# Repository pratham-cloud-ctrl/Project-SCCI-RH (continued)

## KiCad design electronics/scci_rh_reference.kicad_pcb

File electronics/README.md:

# SCCI_RH analog reference

An editable, routed **5 V artificial-signal / electrical-test-load circuit**.
It is one recording channel and one fixed-current biphasic load channel. It is
not implant electronics and contains no populated ADC, processor or biological
interface.

Open **`scci_rh_reference.kicad_pro`** in KiCad 10.0.6 or later. Local symbols,
footprints and component STEP models accompany the project. The 80 x 50 x
1.6 mm board has four 3.2 mm mounting holes at (10,10), (70,10), (10,40), (70,40).

- [Circuit explanation and boundaries](../docs/electronics.md)
- [Schematic PDF](exports/scci_rh_reference_schematic.pdf)
- [BOM](bom.csv)
- [Native board](scci_rh_reference.kicad_pcb)
- [Board STEP](exports/scci_rh_reference.step)
- [Gerber and drill reference exports](exports/gerbers/)
- [ERC report](reports/erc.json) and [DRC/parity report](reports/drc.json)
- [Model parameters](simulation/parameters.json) and [results](simulation/metrics.json)
- [Generic-device SPICE circuit](simulation/current_sink_generic.cir)
- [Third-party library licenses](THIRD_PARTY_LICENSES.md)

The retained reports have zero ERC violations, zero PCB DRC violations, zero
unconnected items and zero schematic parity issues, with no excluded violations.
Those checks establish connectivity/layout consistency, not analog stability.
The generic-device SPICE study exposed an unprotected switching transient;
revision B adds two 12 kΩ output resistors and reduces the nominal modeled peak
from 1361.36 to 102.58 μA. The before/after evidence is retained. The load and
parasitic assumptions remain conditional; no universal current cap is claimed.
Do not infer fabrication readiness or biological safety from a clean rule report.

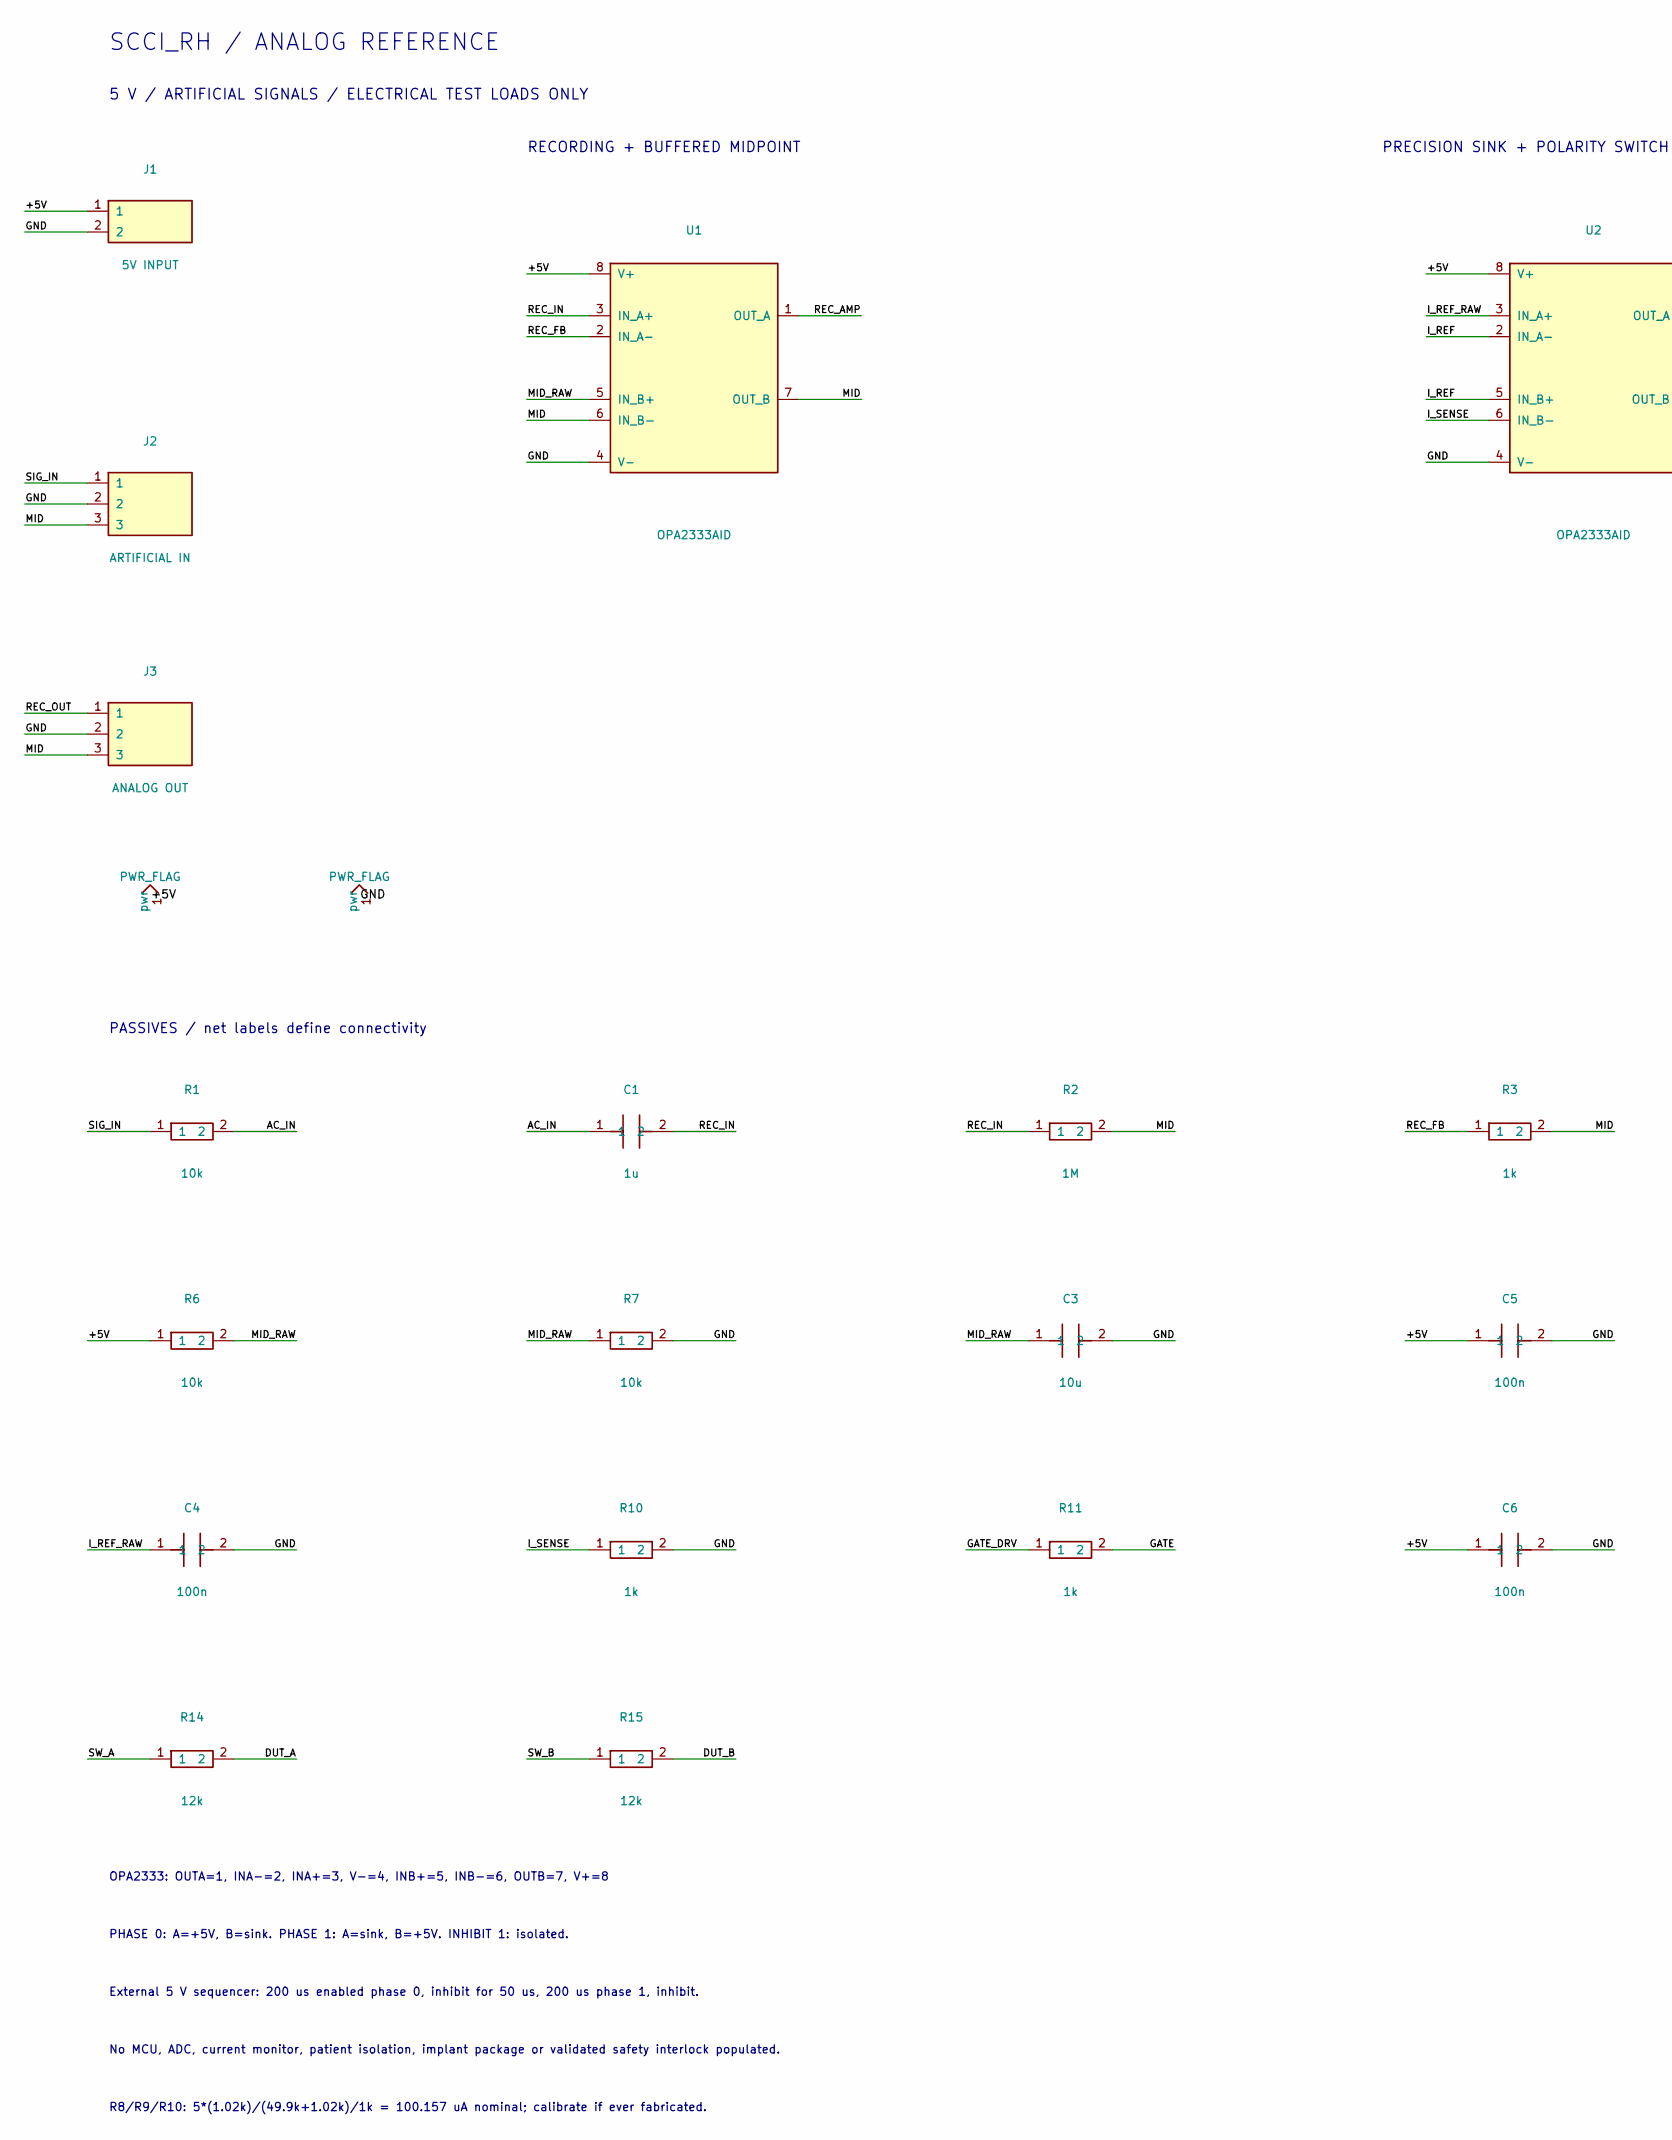
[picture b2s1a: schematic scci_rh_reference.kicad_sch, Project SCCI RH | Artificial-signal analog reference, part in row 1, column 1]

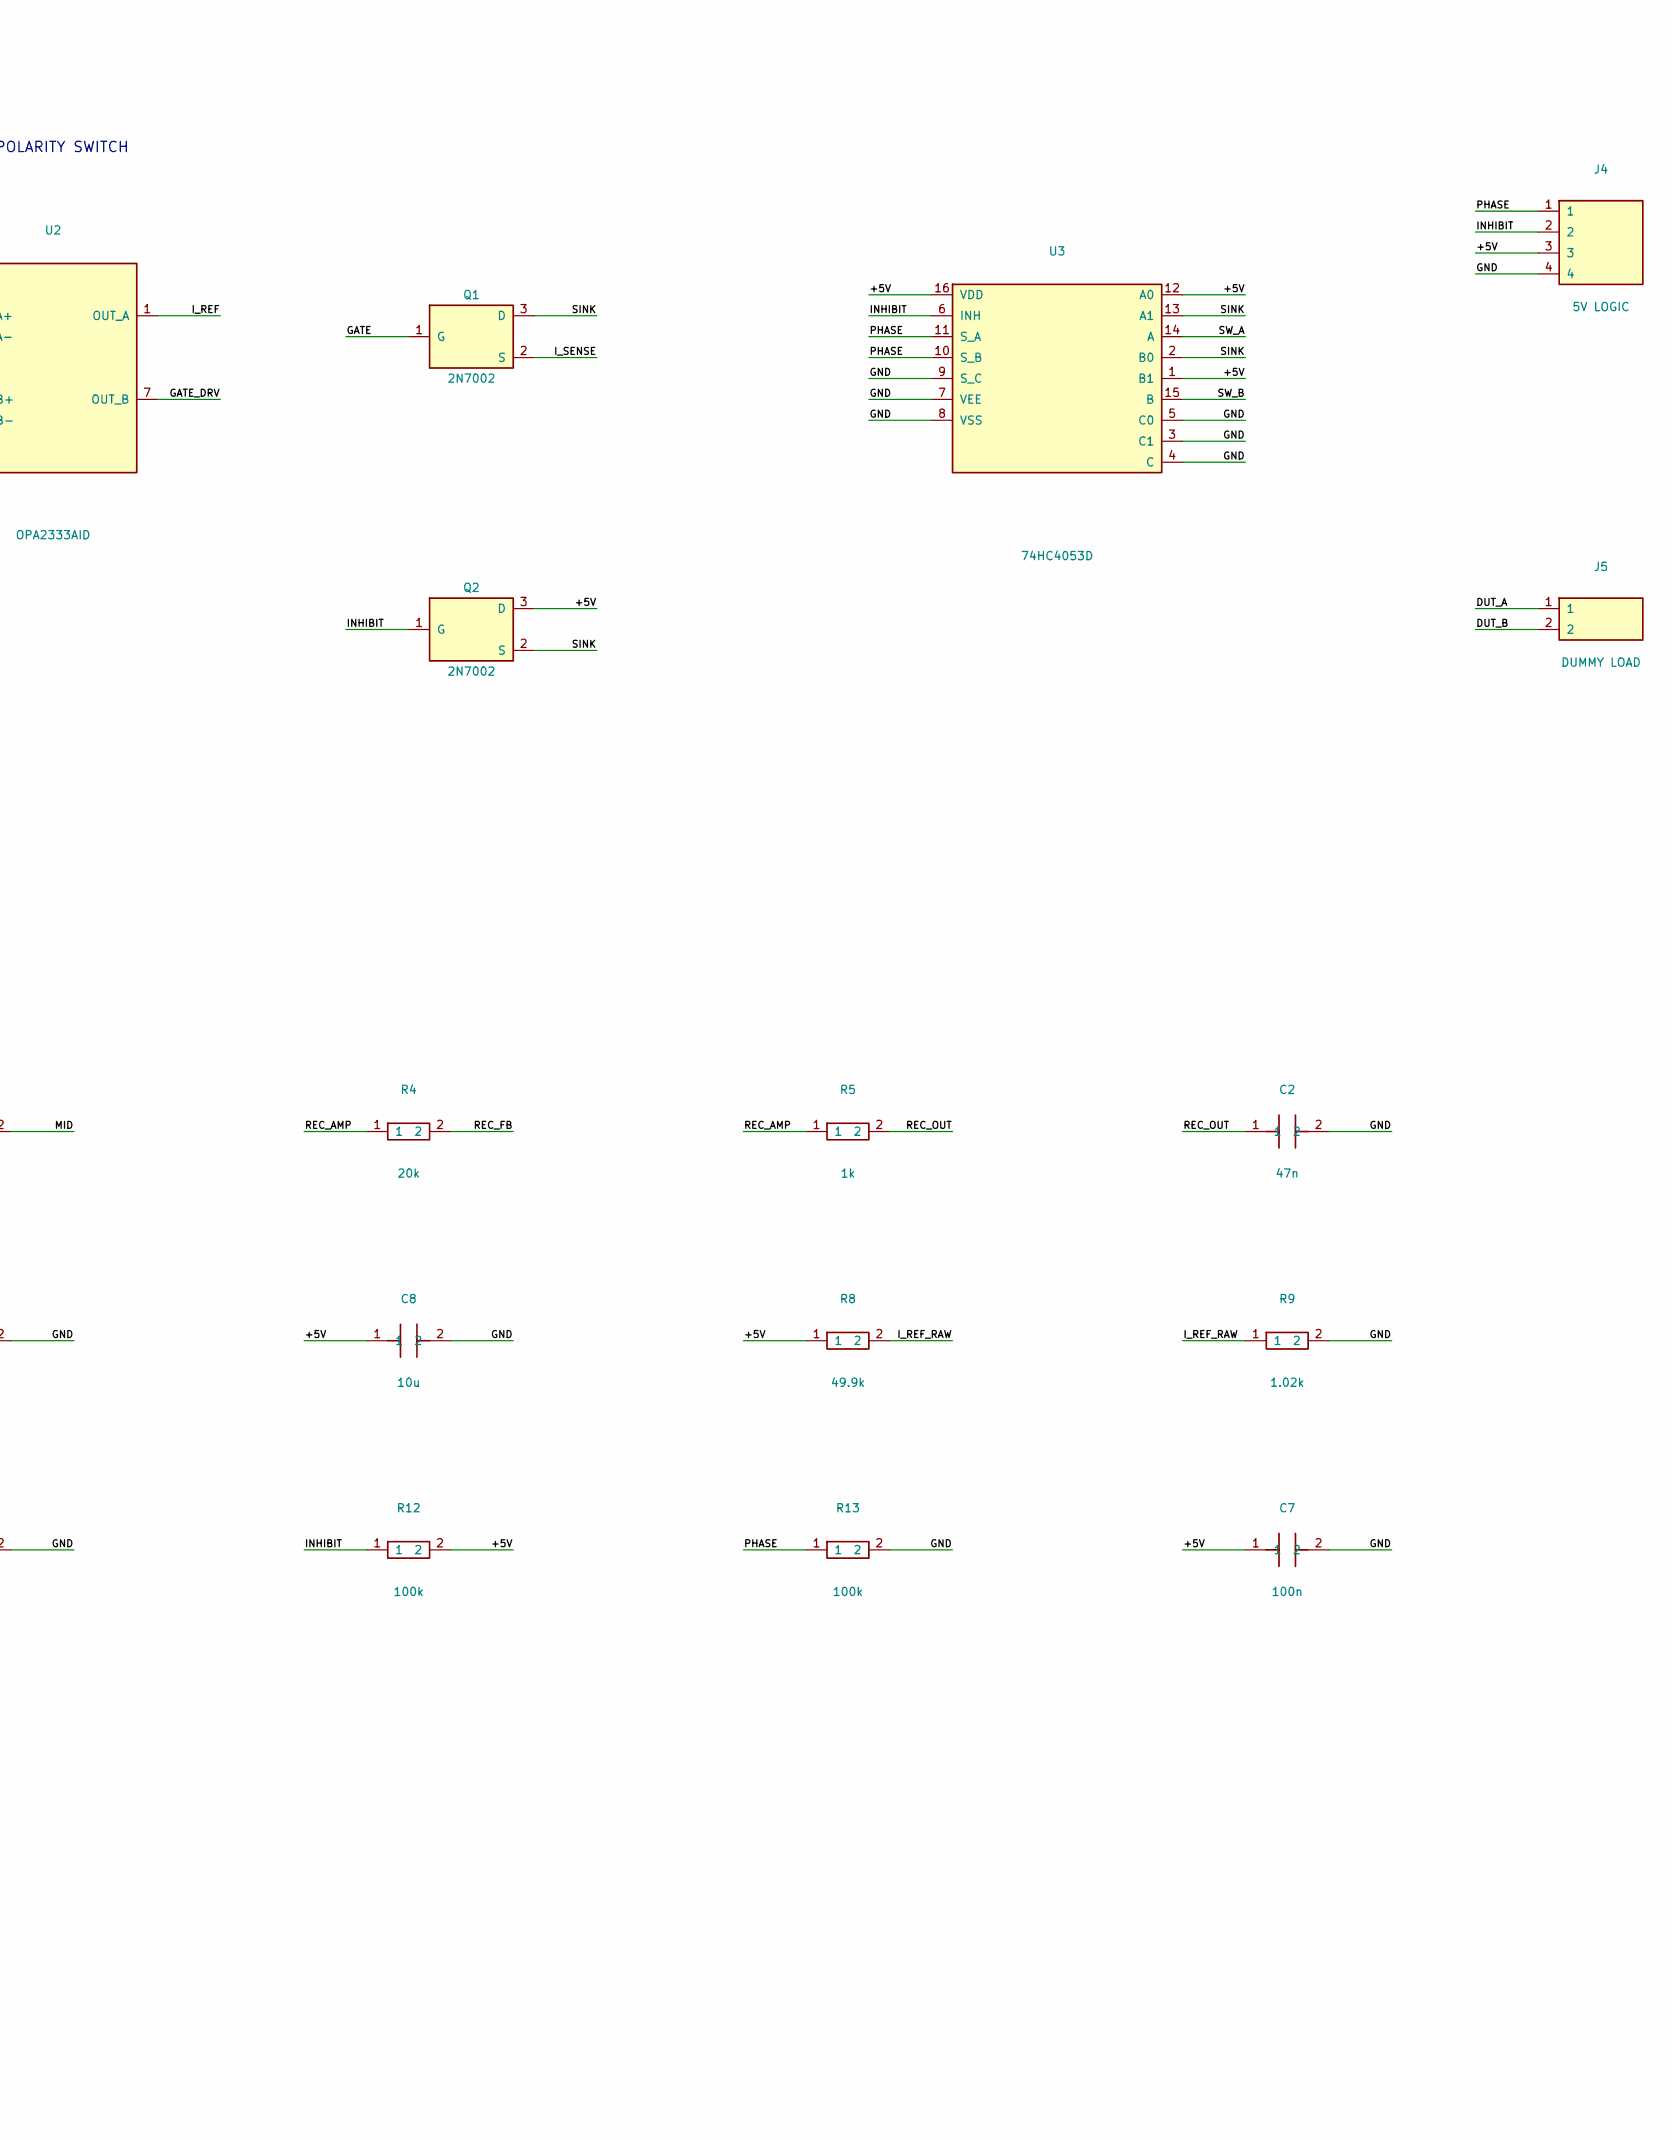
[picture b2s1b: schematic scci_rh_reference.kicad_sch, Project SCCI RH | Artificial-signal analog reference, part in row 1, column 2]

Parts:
C1: 1u; C_0805_2012Metric
C2: 47n; C_0805_2012Metric
C3, C8: 10u; C_0805_2012Metric
C4, C5, C6, C7: 100n; C_0805_2012Metric
J1: 5V INPUT; PinHeader_1x02_P2.54mm_Vertical
J2: ARTIFICIAL IN; PinHeader_1x03_P2.54mm_Vertical
J3: ANALOG OUT; PinHeader_1x03_P2.54mm_Vertical
J4: 5V LOGIC; PinHeader_1x04_P2.54mm_Vertical
J5: DUMMY LOAD; PinHeader_1x02_P2.54mm_Vertical
Q1, Q2: 2N7002; SOT-23
R1, R6, R7: 10k; R_0805_2012Metric
R2: 1M; R_0805_2012Metric
R3, R5, R10, R11: 1k; R_0805_2012Metric
R4: 20k; R_0805_2012Metric
R8: 49.9k; R_0805_2012Metric
R9: 1.02k; R_0805_2012Metric
R12, R13: 100k; R_0805_2012Metric
R14, R15: 12k; R_0805_2012Metric
U1, U2: OPA2333AID; SOIC-8_3.9x4.9mm_P1.27mm
U3: 74HC4053D; SOIC-16_3.9x9.9mm_P1.27mm

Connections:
/+5V: C5.1, C6.1, C7.1, C8.1, J1.1, J4.3, Q2.3 (D), R6.1, R8.1, R12.2, U1.8 (V+), U2.8 (V+), U3.1 (B1), U3.12 (A0), U3.16 (VDD)
/AC_IN: C1.1, R1.2
/DUT_A: J5.1, R14.2
/DUT_B: J5.2, R15.2
/GATE: Q1.1 (G), R11.2
/GATE_DRV: R11.1, U2.7 (OUT_B)
/GND: C2.2, C3.2, C4.2, C5.2, C6.2, C7.2, C8.2, J1.2, J2.2, J3.2, J4.4, R7.2, R9.2, R10.2, R13.2, U1.4 (V-), U2.4 (V-), U3.3 (C1), U3.4 (C), U3.5 (C0), U3.7 (VEE), U3.8 (VSS), U3.9 (S_C)
/INHIBIT: J4.2, Q2.1 (G), R12.1, U3.6 (INH)
/I_REF: U2.1 (OUT_A), U2.2 (IN_A-), U2.5 (IN_B+)
/I_REF_RAW: C4.1, R8.2, R9.1, U2.3 (IN_A+)
/I_SENSE: Q1.2 (S), R10.1, U2.6 (IN_B-)
/MID: J2.3, J3.3, R2.2, R3.2, U1.6 (IN_B-), U1.7 (OUT_B)
/MID_RAW: C3.1, R6.2, R7.1, U1.5 (IN_B+)
/PHASE: J4.1, R13.1, U3.10 (S_B), U3.11 (S_A)
/REC_AMP: R4.1, R5.1, U1.1 (OUT_A)
/REC_FB: R3.1, R4.2, U1.2 (IN_A-)
/REC_IN: C1.2, R2.1, U1.3 (IN_A+)
/REC_OUT: C2.1, J3.1, R5.2
/SIG_IN: J2.1, R1.1
/SINK: Q1.3 (D), Q2.2 (S), U3.2 (B0), U3.13 (A1)
/SW_A: R14.1, U3.14 (A)
/SW_B: R15.1, U3.15 (B)

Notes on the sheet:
SCCI_RH / ANALOG REFERENCE
5 V / ARTIFICIAL SIGNALS / ELECTRICAL TEST LOADS ONLY
RECORDING + BUFFERED MIDPOINT
PRECISION SINK + POLARITY SWITCH
PASSIVES / net labels define connectivity
OPA2333: OUTA=1, INA-=2, INA+=3, V-=4, INB+=5, INB-=6, OUTB=7, V+=8
PHASE 0: A=+5V, B=sink. PHASE 1: A=sink, B=+5V. INHIBIT 1: isolated.
External 5 V sequencer: 200 us enabled phase 0, inhibit for 50 us, 200 us phase 1, inhibit.
No MCU, ADC, current monitor, patient isolation, implant package or validated safety interlock populated.
R8/R9/R10: 5*(1.02k)/(49.9k+1.02k)/1k = 100.157 uA nominal; calibrate if ever fabricated.

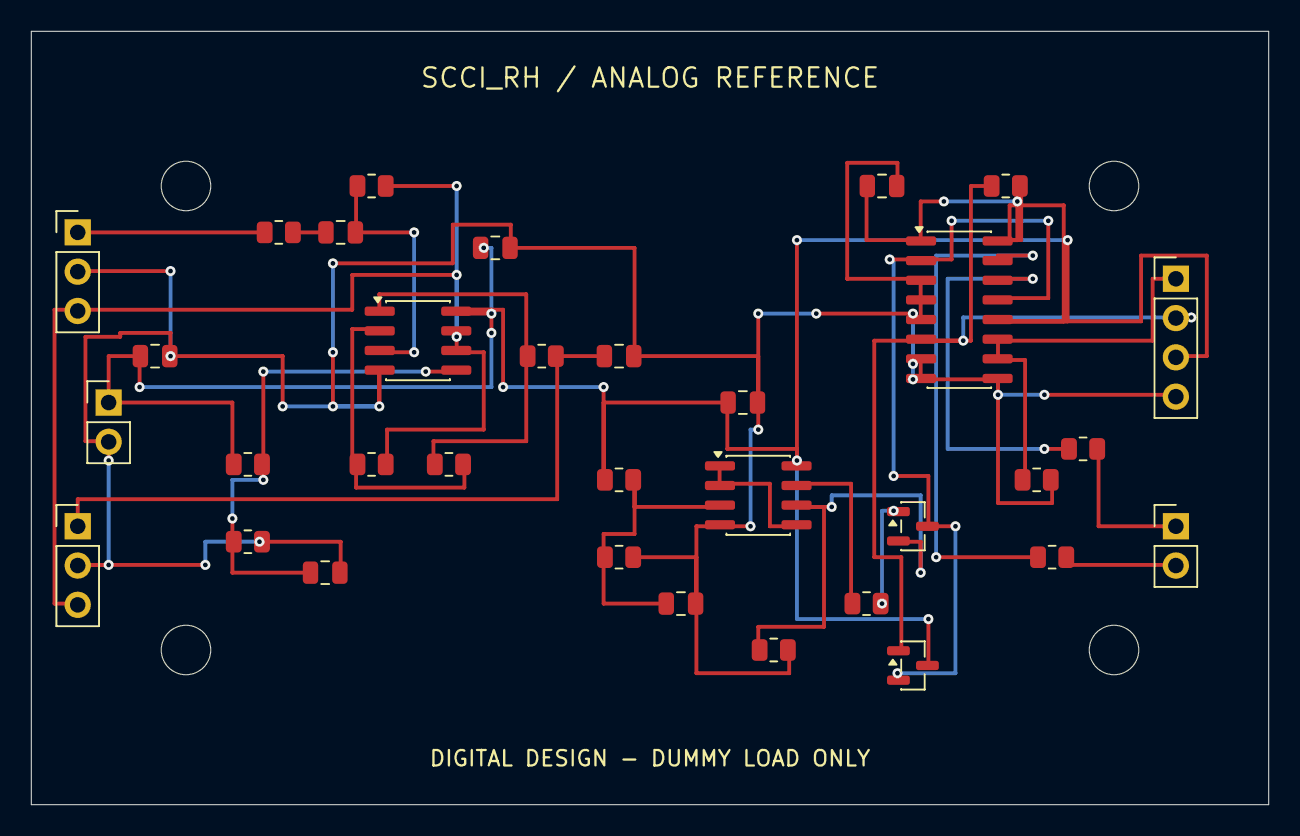
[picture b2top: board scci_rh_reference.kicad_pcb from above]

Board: 2 copper layers, 80.0 x 50.0 mm, 37 parts (0 on the bottom side), 22 nets.

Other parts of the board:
H1, H2, H3, H4: MountingHole_3.2mm_M3

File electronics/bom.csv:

Reference,Value,Footprint,MPN or specification,Function
J1,5V INPUT,scci_rh:PinHeader_1x02_P2.54mm_Vertical,,External regulated 5 V only; no isolation or regulator
J2,ARTIFICIAL IN,scci_rh:PinHeader_1x03_P2.54mm_Vertical,,Function-generator input and midpoint monitor
J3,ANALOG OUT,scci_rh:PinHeader_1x03_P2.54mm_Vertical,,"High-impedance external ADC/scope, not populated"
U1,OPA2333AID,scci_rh:SOIC-8_3.9x4.9mm_P1.27mm,OPA2333AID,A: AC-coupled gain 21; B: midpoint follower
R1,10k,scci_rh:R_0805_2012Metric,"0805 thin-film, 0.1%, >=0.125 W",Input series impedance; not patient protection
C1,1u,scci_rh:C_0805_2012Metric,"0805 ceramic, X7R, >=10 V, 10%","Input AC coupling, 0.158 Hz corner with R1+R2"
R2,1M,scci_rh:R_0805_2012Metric,"0805 thin-film, 0.1%, >=0.125 W",Amplifier input bias return
R3,1k,scci_rh:R_0805_2012Metric,"0805 thin-film, 0.1%, >=0.125 W",Gain denominator
R4,20k,scci_rh:R_0805_2012Metric,"0805 thin-film, 0.1%, >=0.125 W",Gain numerator
R5,1k,scci_rh:R_0805_2012Metric,"0805 thin-film, 0.1%, >=0.125 W",Output RC and capacitive-load isolation
C2,47n,scci_rh:C_0805_2012Metric,"0805 ceramic, X7R, >=10 V, 10%",Output low-pass capacitor
R6,10k,scci_rh:R_0805_2012Metric,"0805 thin-film, 0.1%, >=0.125 W",Midpoint divider upper
R7,10k,scci_rh:R_0805_2012Metric,"0805 thin-film, 0.1%, >=0.125 W",Midpoint divider lower
C3,10u,scci_rh:C_0805_2012Metric,"0805 ceramic, X7R, >=10 V, 10%",Midpoint bulk bypass
C5,100n,scci_rh:C_0805_2012Metric,"0805 ceramic, X7R, >=10 V, 10%",U1 local supply bypass
C8,10u,scci_rh:C_0805_2012Metric,"0805 ceramic, X7R, >=10 V, 10%",Input supply bulk bypass
U2,OPA2333AID,scci_rh:SOIC-8_3.9x4.9mm_P1.27mm,OPA2333AID,A: reference follower; B: current servo
R8,49.9k,scci_rh:R_0805_2012Metric,"0805 thin-film, 0.1%, >=0.125 W",Current-reference divider upper
R9,1.02k,scci_rh:R_0805_2012Metric,"0805 thin-film, 0.1%, >=0.125 W",Current-reference divider lower
C4,100n,scci_rh:C_0805_2012Metric,"0805 ceramic, X7R, >=10 V, 10%",Reference low-pass
R10,1k,scci_rh:R_0805_2012Metric,"0805 thin-film, 0.1%, >=0.125 W","Current sense, I = Vref / R10"
R11,1k,scci_rh:R_0805_2012Metric,"0805 thin-film, 0.1%, >=0.125 W",MOSFET gate isolation
Q1,2N7002,scci_rh:SOT-23,2N7002,N-MOSFET current sink; stability not hardware-validated
Q2,2N7002,scci_rh:SOT-23,2N7002,Idle source-follower bypass keeps sink servo supplied while INHIBIT=1
C6,100n,scci_rh:C_0805_2012Metric,"0805 ceramic, X7R, >=10 V, 10%",U2 local supply bypass
U3,74HC4053D,scci_rh:SOIC-16_3.9x9.9mm_P1.27mm,74HC4053D,A/B SPDT sections reverse one regulated sink; C grounded unused
R12,100k,scci_rh:R_0805_2012Metric,"0805 thin-film, 0.1%, >=0.125 W",Default-off pull-up; externally driven low to enable
R13,100k,scci_rh:R_0805_2012Metric,"0805 thin-film, 0.1%, >=0.125 W",Defined polarity while logic is disconnected
C7,100n,scci_rh:C_0805_2012Metric,"0805 ceramic, X7R, >=10 V, 10%",U3 local supply bypass
R14,12k,scci_rh:R_0805_2012Metric,"0805 thin-film, 0.1%, >=0.125 W","Revision B series output resistance, leg A"
R15,12k,scci_rh:R_0805_2012Metric,"0805 thin-film, 0.1%, >=0.125 W","Revision B series output resistance, leg B"
J4,5V LOGIC,scci_rh:PinHeader_1x04_P2.54mm_Vertical,,External phase/inhibit sequencer; 5 V CMOS logic required
J5,DUMMY LOAD,scci_rh:PinHeader_1x02_P2.54mm_Vertical,,External electrical test load only

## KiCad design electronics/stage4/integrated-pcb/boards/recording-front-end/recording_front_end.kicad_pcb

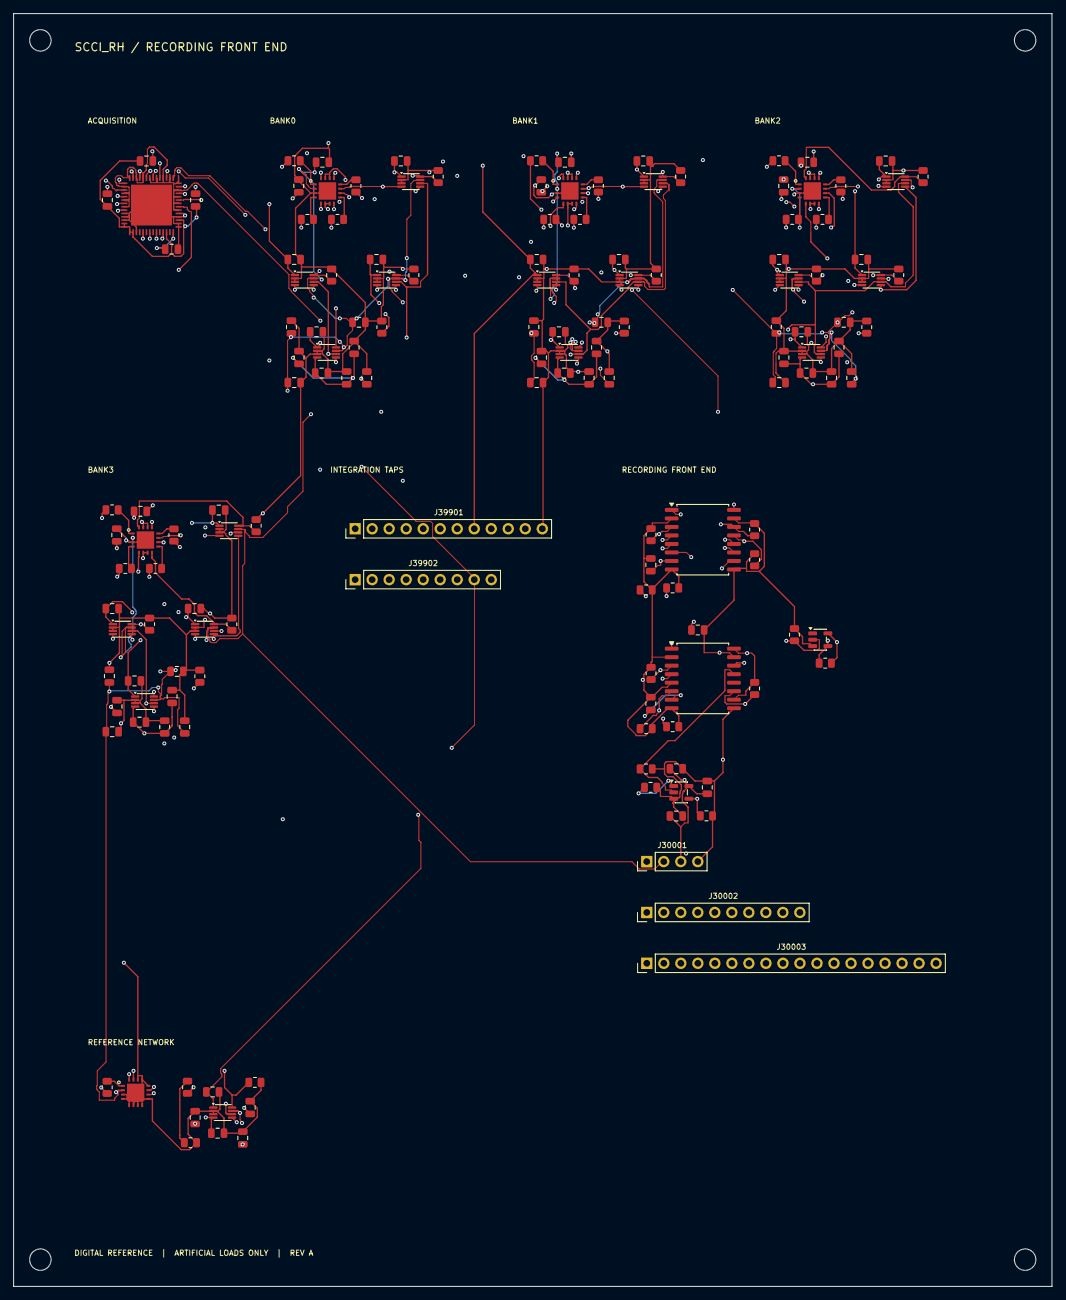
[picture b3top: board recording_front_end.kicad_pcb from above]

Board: 4 copper layers, 155.0 x 190.0 mm, 157 parts (0 on the bottom side), 93 nets.

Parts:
C30001, C30002, C30003, C30004, C30005, C30006, C30010, C30011, C30020, C30021, C30022, C30023, C30030, C30031, C30032, C30033, C30200, C30201, C30202, C30203, C30204, C30205, C30206, C30207, C30208, C30209, C30210, C30211, C30212, C30213, C30214, C30215, C30300, C30301, C30302, C30303, C30304, C30305, C30306, C30307, C30308, C30309, C30310, C30311, C30312, C30313, C30314, C30315, C30510, C30511, C30512, C30513: 100n X7R 16V; C_0805_2012Metric
C30012: 10n 16V; C_0805_2012Metric
C30013: 1u X7R 16V; C_0805_2012Metric
C30100, C30101, C30102, C30103, C30104, C30105, C30106, C30107, C30108, C30109, C30110, C30111, C30112, C30113, C30114, C30115: 470p C0G 50V; C_0805_2012Metric
C30500: 2.2n C0G 50V; C_0805_2012Metric
H1, H2, H3, H4: MountingHole_3.2mm_M3
J30001: EXTERNAL ISOLATED AFE RAILS; PinHeader_1x04_P2.54mm_Vertical
J30002: HOST SPI / SUPERVISOR; PinHeader_1x10_P2.54mm_Vertical
J30003: 18 RECORDING FUNCTIONAL PORTS; PinHeader_1x18_P2.54mm_Vertical
J39901: AFE TAP HARNESS; PinHeader_1x12_P2.54mm_Vertical
J39902: AFE TAP HARNESS; PinHeader_1x09_P2.54mm_Vertical
R30001, R30002, R30003, R30004, R30005, R30006, R30007, R30008, R30009, R30010, R30011, R30012, R30013: 10k; R_0805_2012Metric
R30014: 1k; R_0805_2012Metric
R30100, R30101, R30102, R30103, R30104, R30105, R30106, R30107, R30108, R30109, R30110, R30111, R30112, R30113, R30114, R30115, R30500: 4.99k 0.1%; R_0805_2012Metric
R30200, R30201, R30202, R30203, R30204, R30205, R30206, R30207, R30208, R30209, R30210, R30211, R30212, R30213, R30214, R30215, R30501: 10M; R_0805_2012Metric
R30502, R30503: 499k 0.1%; R_0805_2012Metric
U30001, U30002: ISO6741FDWR; SOIC-16W_7.5x10.3mm_P1.27mm
U30003: SN74LVC1G04DBVR; SOT-23-5
U30004: SN74LVC1G08DBVR; SOT-23-5
U30010: RHD2216; RHD2216_QFN56_8x8_P0.5_EP6.1
U30020, U30021, U30022, U30023, U30024: TMUX7412FRRPR; Texas_RRP0016A_WQFN16_4x4_P0.65_EP2.6
U30100, U30101, U30102, U30103, U30104, U30105, U30106, U30107, U30108, U30109, U30110, U30111, U30112, U30113, U30114, U30115, U30500: TMUX6219DGKR; VSSOP-8_2.3x2mm_P0.5mm

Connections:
SYS_0bc4e447__AFE_CONNECT: J39901.2, R30007.1, U30002.14, U30004.1, U30020.6, U30020.7, U30020.14, U30020.15, U30021.6, U30021.7, U30021.14, U30021.15, U30022.6, U30022.7, U30022.14, U30022.15, U30023.6, U30023.7, U30023.14, U30023.15, U30024.15
SYS_1dc2a435__AFE_IN08_P: C30108.1, J39901.11, U30010.49, U30108.1
SYS_3fdd5066__AFE_P5: C30020.1, C30021.1, C30022.1, C30023.1, C30200.1, C30201.1, C30202.1, C30203.1, C30204.1, C30205.1, C30206.1, C30207.1, C30208.1, C30209.1, C30210.1, C30211.1, C30212.1, C30213.1, C30214.1, C30215.1, C30510.1, C30512.1, J30001.1, U30020.11, U30021.11, U30022.11, U30023.11, U30024.11, U30100.4, U30101.4, U30102.4, U30103.4, U30104.4, U30105.4, U30106.4, U30107.4, U30108.4, U30109.4, U30110.4, U30111.4, U30112.4, U30113.4, U30114.4, U30115.4, U30500.4
SYS_4d4028f1__AFE_MOSI: J30002.4, R30002.1, U30001.4
SYS_4dbe75ce__AFE_MISO: J30002.6, U30001.6
SYS_4eb6b999__AFE_ACQUIRE: J39901.1, R30009.1, U30004.4, U30100.6, U30101.6, U30102.6, U30103.6, U30104.6, U30105.6, U30106.6, U30107.6, U30108.6, U30109.6, U30110.6, U30111.6, U30112.6, U30113.6, U30114.6, U30115.6, U30500.6
SYS_4f7d5988__AFE_IN14_P: C30114.1, J39902.6, U30010.37, U30114.1
SYS_4fabccc5__AFE_IN12_P: C30112.1, J39902.4, U30010.41, U30112.1
SYS_7e367734__AFE_IN04_P: C30104.1, J39901.7, U30010.1, U30104.1
SYS_8b29b23f__AFE_CONNECT: J30002.7, R30004.1, U30002.3
SYS_8c3f25bb__AFE_IN02_P: C30102.1, J39901.5, U30010.5, U30102.1
SYS_18e49fe8__AFE_CS_ASSERT: J30002.5, R30003.1, U30001.5
SYS_32c4c1cc__AFE_IN13_P: C30113.1, J39902.5, U30010.39, U30113.1
SYS_65aafbb6__AFE_3V3: C30002.1, C30004.1, C30005.1, C30006.1, C30010.1, C30011.1, C30013.1, J30001.3, R30011.2, R30014.2, U30001.10, U30001.16, U30002.10, U30002.16, U30003.5, U30004.5, U30010.13, U30010.14, U30010.15, U30010.16, U30010.26, U30010.31, U30100.5, U30101.5, U30102.5, U30103.5, U30104.5, U30105.5, U30106.5, U30107.5, U30108.5, U30109.5, U30110.5, U30111.5, U30112.5, U30113.5, U30114.5, U30115.5, U30500.5
SYS_86b728f8__AFE_REF: C30500.1, J39902.8, U30010.2, U30010.4, U30010.6, U30010.8, U30010.34, U30010.36, U30010.38, U30010.40, U30010.42, U30010.44, U30010.46, U30010.48, U30010.50, U30010.52, U30010.54, U30010.56, U30500.1
SYS_96d7c46a__AFE_IN10_P: C30110.1, J39902.2, U30010.45, U30110.1
SYS_3232ae4c__AFE_IN01_P: C30101.1, J39901.4, U30010.7, U30101.1
SYS_53213f89__AFE_IN15_P: C30115.1, J39902.7, U30010.35, U30115.1
SYS_56562df4__GND: C30001.2, C30003.2, J30002.2, J30002.10, R30001.2, R30002.2, R30003.2, R30004.2, R30005.2, R30006.2, U30001.2, U30001.8, U30002.2, U30002.5, U30002.8
SYS_59100ef9__AFE_IN05_P: C30105.1, J39901.8, U30010.55, U30105.1
SYS_325713b8__AFE_IN07_P: C30107.1, J39901.10, U30010.51, U30107.1
SYS_380216f6__AFE_IN06_P: C30106.1, J39901.9, U30010.53, U30106.1
SYS_05097029__AFE_IN00_P: C30100.1, J39901.3, U30010.9, U30100.1
SYS_08572049__HOST_3V3: C30001.1, C30003.1, J30002.1, U30001.1, U30001.7, U30002.1, U30002.7
SYS_a9673f8c__AFE_RECORD: J30002.8, R30005.1, U30002.4
SYS_b6a4cd67__AFE_IN11_P: C30111.1, J39902.3, U30010.43, U30111.1
SYS_ce1178b4__AFE_FAULT_N: J30002.9, R30006.1, U30002.6
SYS_d73cd2ee__AFE_N5: C30030.1, C30031.1, C30032.1, C30033.1, C30300.1, C30301.1, C30302.1, C30303.1, C30304.1, C30305.1, C30306.1, C30307.1, C30308.1, C30309.1, C30310.1, C30311.1, C30312.1, C30313.1, C30314.1, C30315.1, C30511.1, C30513.1, J30001.2, U30020.2, U30021.2, U30022.2, U30023.2, U30024.2, U30100.7, U30101.7, U30102.7, U30103.7, U30104.7, U30105.7, U30106.7, U30107.7, U30108.7, U30109.7, U30110.7, U30111.7, U30112.7, U30113.7, U30114.7, U30115.7, U30500.7
SYS_ee730a89__AFE_IN09_P: C30109.1, J39902.1, U30010.47, U30109.1
SYS_f30c60de__AFE_SCLK: J30002.3, R30001.1, U30001.3
SYS_f208be39__AFE_IN03_P: C30103.1, J39901.6, U30010.3, U30103.1
SYS_fca1c340__AFEAGND: C30002.2, C30004.2, C30005.2, C30006.2, C30010.2, C30011.2, C30012.2, C30013.2, C30020.2, C30021.2, C30022.2, C30023.2, C30030.2, C30031.2, C30032.2, C30033.2, C30100.2, C30101.2, C30102.2, C30103.2, C30104.2, C30105.2, C30106.2, C30107.2, C30108.2, C30109.2, C30110.2, C30111.2, C30112.2, C30113.2, C30114.2, C30115.2, C30200.2, C30201.2, C30202.2, C30203.2, C30204.2, C30205.2, C30206.2, C30207.2, C30208.2, C30209.2, C30210.2, C30211.2, C30212.2, C30213.2, C30214.2, C30215.2, C30300.2, C30301.2, C30302.2, C30303.2, C30304.2, C30305.2, C30306.2, C30307.2, C30308.2, C30309.2, C30310.2, C30311.2, C30312.2, C30313.2, C30314.2, C30315.2, C30500.2, C30510.2, C30511.2, C30512.2, C30513.2, J30001.4, J39901.12, J39902.9, R30007.2, R30008.2, R30009.2, R30010.2, R30012.2, R30013.2, R30200.2, R30201.2, R30202.2, R30203.2, R30204.2, R30205.2, R30206.2, R30207.2, R30208.2, R30209.2, R30210.2, R30211.2, R30212.2, R30213.2, R30214.2, R30215.2, R30501.2, R30503.2, U30001.9, U30001.15, U30002.9, U30002.15, U30003.3, U30004.3, U30010.10, U30010.11, U30010.12, U30010.17, U30010.29, U30010.30, U30010.32, U30010.33, U30010.57, U30020.3, U30020.17, U30021.3, U30021.17, U30022.3, U30022.17, U30023.3, U30023.17, U30024.3, U30024.4, U30024.5, U30024.6, U30024.7, U30024.8, U30024.9, U30024.12, U30024.13, U30024.14, U30024.17, U30100.2, U30100.3, U30101.2, U30101.3, U30102.2, U30102.3, U30103.2, U30103.3, U30104.2, U30104.3, U30105.2, U30105.3, U30106.2, U30106.3, U30107.2, U30107.3, U30108.2, U30108.3, U30109.2, U30109.3, U30110.2, U30110.3, U30111.2, U30111.3, U30112.2, U30112.3, U30113.2, U30113.3, U30114.2, U30114.3, U30115.2, U30115.3, U30500.2, U30500.3
recording-front-end__AFE_ADC_REF: C30012.1, U30010.28
recording-front-end__AFE_CS_ASSERT: R30010.1, U30001.12, U30003.2
recording-front-end__AFE_CS_N: R30011.1, U30003.4, U30010.19
recording-front-end__AFE_FAULT_N: R30014.1, U30002.11, U30020.10, U30021.10, U30022.10, U30023.10, U30024.10
recording-front-end__AFE_MISO: U30001.11, U30010.25
recording-front-end__AFE_MOSI: R30013.1, U30001.13, U30010.23
recording-front-end__AFE_RECORD_CMD: R30008.1, U30002.13, U30004.2
recording-front-end__AFE_SCLK: R30012.1, U30001.14, U30010.21
recording-front-end__BIAS_CONTACT: J30003.18, R30502.1
recording-front-end__BIAS_MID: R30502.2, R30503.1
recording-front-end__REC00_CONTACT: J30003.1, R30100.1
recording-front-end__REC00_PROT: R30200.1, U30020.16, U30100.8
recording-front-end__REC00_SERIES: R30100.2, U30020.1
recording-front-end__REC01_CONTACT: J30003.2, R30101.1
recording-front-end__REC01_PROT: R30201.1, U30020.13, U30101.8
recording-front-end__REC01_SERIES: R30101.2, U30020.12
recording-front-end__REC02_CONTACT: J30003.3, R30102.1
recording-front-end__REC02_PROT: R30202.1, U30020.8, U30102.8
recording-front-end__REC02_SERIES: R30102.2, U30020.9
recording-front-end__REC03_CONTACT: J30003.4, R30103.1
recording-front-end__REC03_PROT: R30203.1, U30020.5, U30103.8
recording-front-end__REC03_SERIES: R30103.2, U30020.4
recording-front-end__REC04_CONTACT: J30003.5, R30104.1
recording-front-end__REC04_PROT: R30204.1, U30021.16, U30104.8
recording-front-end__REC04_SERIES: R30104.2, U30021.1
recording-front-end__REC05_CONTACT: J30003.6, R30105.1
recording-front-end__REC05_PROT: R30205.1, U30021.13, U30105.8
recording-front-end__REC05_SERIES: R30105.2, U30021.12
recording-front-end__REC06_CONTACT: J30003.7, R30106.1
recording-front-end__REC06_PROT: R30206.1, U30021.8, U30106.8
recording-front-end__REC06_SERIES: R30106.2, U30021.9
recording-front-end__REC07_CONTACT: J30003.8, R30107.1
recording-front-end__REC07_PROT: R30207.1, U30021.5, U30107.8
recording-front-end__REC07_SERIES: R30107.2, U30021.4
recording-front-end__REC08_CONTACT: J30003.9, R30108.1
recording-front-end__REC08_PROT: R30208.1, U30022.16, U30108.8
recording-front-end__REC08_SERIES: R30108.2, U30022.1
recording-front-end__REC09_CONTACT: J30003.10, R30109.1
recording-front-end__REC09_PROT: R30209.1, U30022.13, U30109.8
recording-front-end__REC09_SERIES: R30109.2, U30022.12
recording-front-end__REC10_CONTACT: J30003.11, R30110.1
recording-front-end__REC10_PROT: R30210.1, U30022.8, U30110.8
recording-front-end__REC10_SERIES: R30110.2, U30022.9
recording-front-end__REC11_CONTACT: J30003.12, R30111.1
recording-front-end__REC11_PROT: R30211.1, U30022.5, U30111.8
recording-front-end__REC11_SERIES: R30111.2, U30022.4
recording-front-end__REC12_CONTACT: J30003.13, R30112.1
recording-front-end__REC12_PROT: R30212.1, U30023.16, U30112.8
recording-front-end__REC12_SERIES: R30112.2, U30023.1
recording-front-end__REC13_CONTACT: J30003.14, R30113.1
recording-front-end__REC13_PROT: R30213.1, U30023.13, U30113.8
recording-front-end__REC13_SERIES: R30113.2, U30023.12
recording-front-end__REC14_CONTACT: J30003.15, R30114.1
recording-front-end__REC14_PROT: R30214.1, U30023.8, U30114.8
recording-front-end__REC14_SERIES: R30114.2, U30023.9
recording-front-end__REC15_CONTACT: J30003.16, R30115.1
recording-front-end__REC15_PROT: R30215.1, U30023.5, U30115.8
recording-front-end__REC15_SERIES: R30115.2, U30023.4
recording-front-end__REF_CONTACT: J30003.17, R30500.1
recording-front-end__REF_PROT: R30501.1, U30024.16, U30500.8
recording-front-end__REF_SERIES: R30500.2, U30024.1
